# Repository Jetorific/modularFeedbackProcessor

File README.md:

# modularFeedbackProcessor
A Eurorack module that delays audio and allows the user to have their own custom effects in the feedback path. All analog design.

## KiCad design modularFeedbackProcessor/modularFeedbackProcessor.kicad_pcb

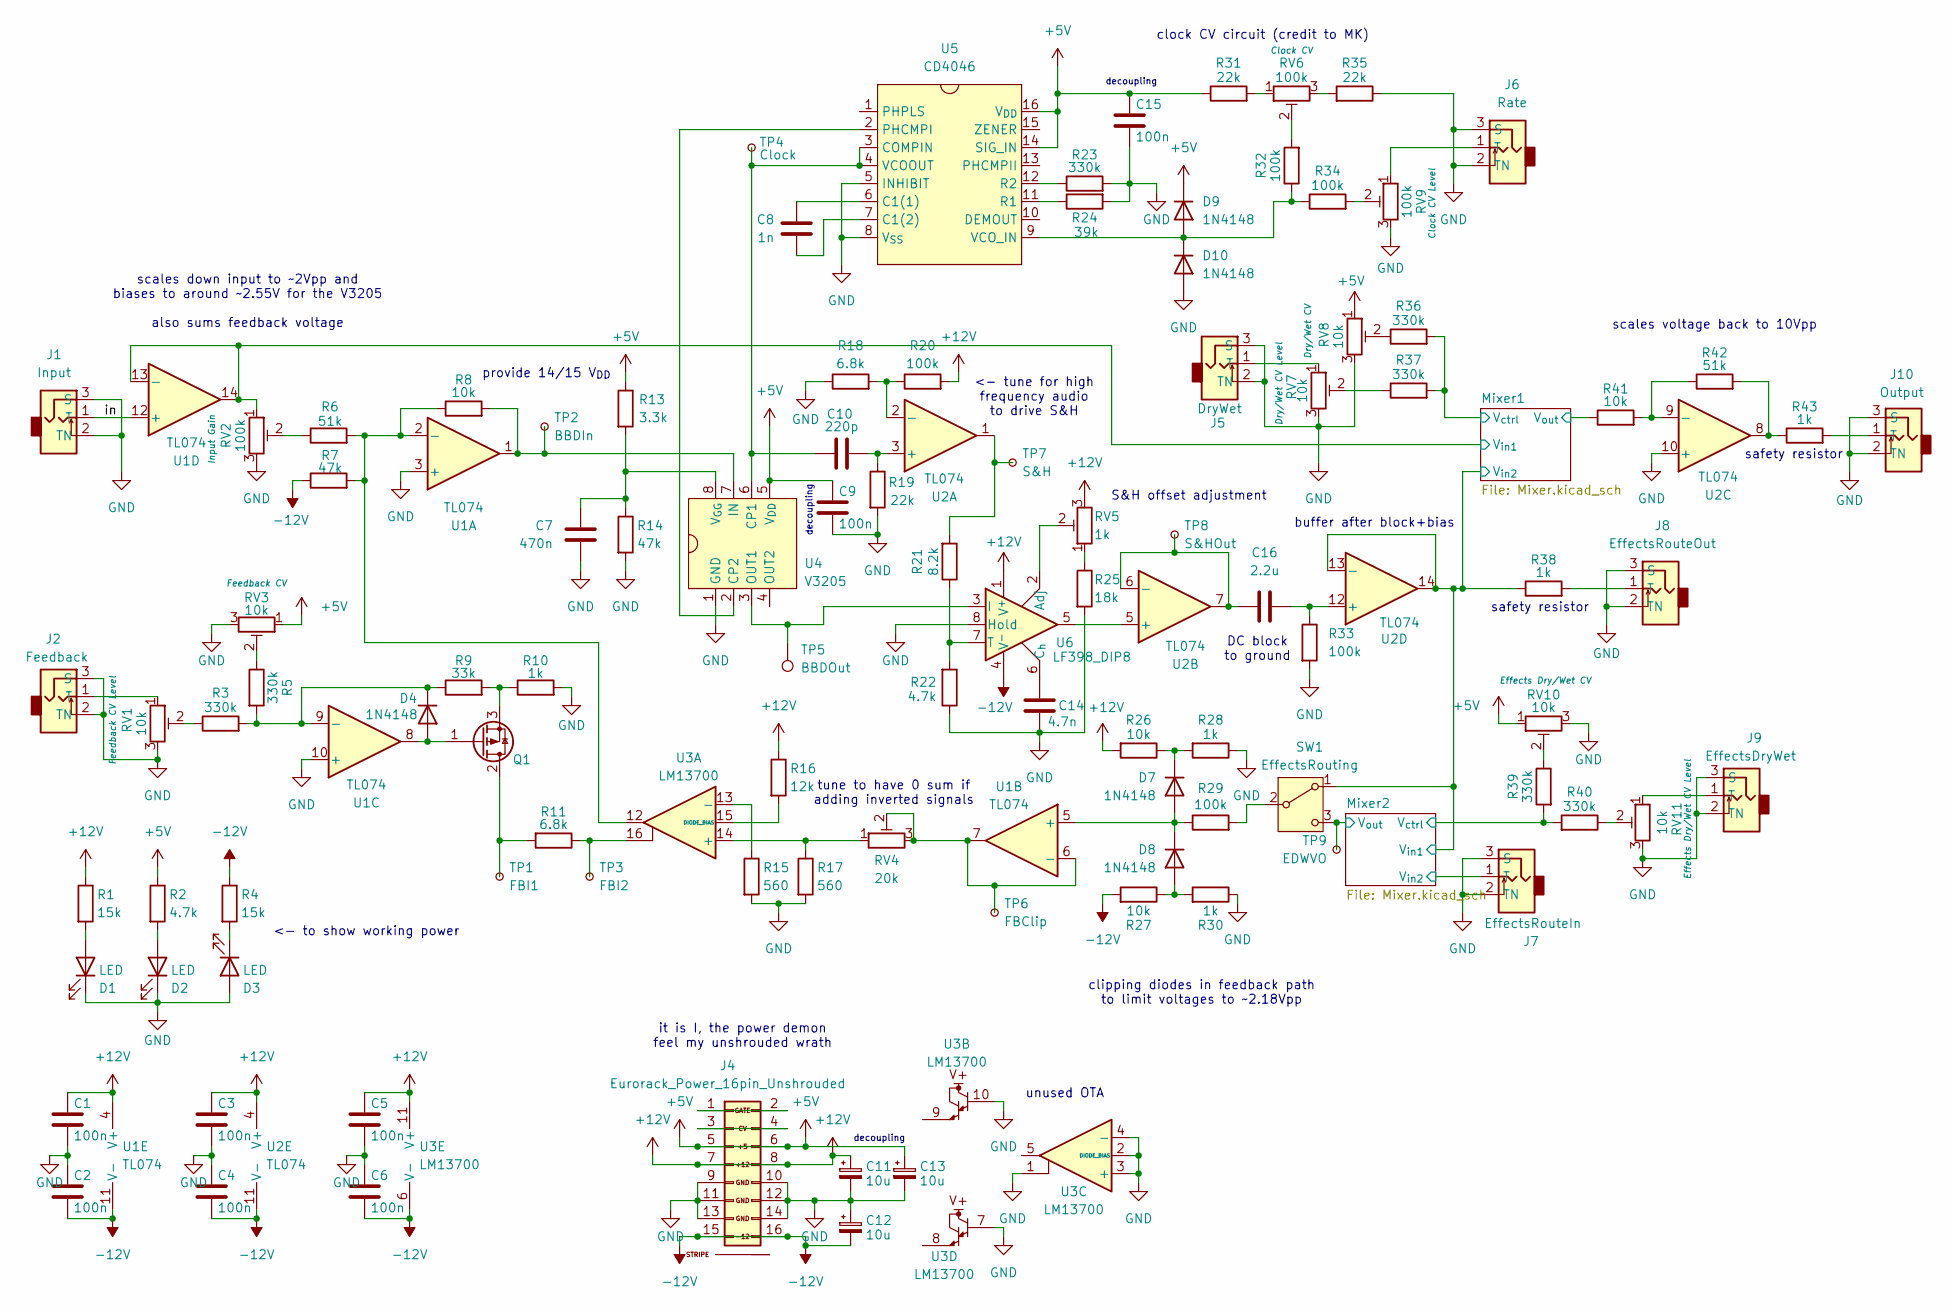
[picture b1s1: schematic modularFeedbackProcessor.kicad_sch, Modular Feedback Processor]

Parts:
C1, C2, C3, C4, C5, C6, C9, C15: 100n; C_0805_2012Metric_Pad1.18x1.45mm_HandSolder
C7: 470n; C_0805_2012Metric_Pad1.18x1.45mm_HandSolder
C8: 1n; C_0805_2012Metric_Pad1.18x1.45mm_HandSolder
C10: 220p; C_0805_2012Metric_Pad1.18x1.45mm_HandSolder
C11, C12, C13: 10u; CP_Radial_D5.0mm_P2.00mm
C14: 4.7n; C_0805_2012Metric_Pad1.18x1.45mm_HandSolder
C16: 2.2u; C_0805_2012Metric_Pad1.18x1.45mm_HandSolder
D1, D2, D3: LED; LED_D5.0mm
D4, D7, D8, D9, D10: 1N4148; D_DO-35_SOD27_P7.62mm_Horizontal
J1: Input; PJ301M-12
J2: Feedback; PJ301M-12
J4: Eurorack_Power_16pin_Unshrouded; Pins_2x08_2.54mm_TH_EuroPower; Part Number 1-1602FBV0T
J5: DryWet; PJ301M-12
J6: Rate; PJ301M-12
J7: EffectsRouteIn; PJ301M-12
J8: EffectsRouteOut; PJ301M-12
J9: EffectsDryWet; PJ301M-12
J10: Output; PJ301M-12
Q1: Q_PMOS_GDS; TO-220-3_Vertical
R1, R4: 15k; R_0805_2012Metric_Pad1.20x1.40mm_HandSolder
R2, R22: 4.7k; R_0805_2012Metric_Pad1.20x1.40mm_HandSolder
R3, R5, R23, R36, R37, R39, R40: 330k; R_0805_2012Metric_Pad1.20x1.40mm_HandSolder
R6, R42: 51k; R_0805_2012Metric_Pad1.20x1.40mm_HandSolder
R7, R14: 47k; R_0805_2012Metric_Pad1.20x1.40mm_HandSolder
R8, R26, R27, R41: 10k; R_0805_2012Metric_Pad1.20x1.40mm_HandSolder
R9: 33k; R_0805_2012Metric_Pad1.20x1.40mm_HandSolder
R10, R28, R30, R38, R43: 1k; R_0805_2012Metric_Pad1.20x1.40mm_HandSolder
R11, R18: 6.8k; R_0805_2012Metric_Pad1.20x1.40mm_HandSolder
R13: 3.3k; R_0805_2012Metric_Pad1.20x1.40mm_HandSolder
R15, R17: 560; R_0805_2012Metric_Pad1.20x1.40mm_HandSolder
R16: 12k; R_0805_2012Metric_Pad1.20x1.40mm_HandSolder
R19, R31, R35: 22k; R_0805_2012Metric_Pad1.20x1.40mm_HandSolder
R20, R29, R32, R33, R34: 100k; R_0805_2012Metric_Pad1.20x1.40mm_HandSolder
R21: 8.2k; R_0805_2012Metric_Pad1.20x1.40mm_HandSolder
R24: 39k; R_0805_2012Metric_Pad1.20x1.40mm_HandSolder
R25: 18k; R_0805_2012Metric_Pad1.20x1.40mm_HandSolder
RV1, RV3, RV7, RV8, RV10, RV11: 10k; Alpha9mmPot
RV2, RV6, RV9: 100k; Alpha9mmPot
RV4: 20k; Potentiometer_Vishay_T73XW_Horizontal
RV5: 1k; Potentiometer_Vishay_T73XW_Horizontal
SW1: EffectsRouting; Switch_Toggle_SPDT_SubMini
TP1: FBI1; TestPoint_Pad_06
TP2: BBDIn; TestPoint_Pad_06
TP3: FBI2; TestPoint_Pad_06
TP4: Clock; TestPoint_Pad_06
TP5: BBDOut; TestPoint_Pad_06
TP6: FBClip; TestPoint_Pad_06
TP7: S&H; TestPoint_Pad_06
TP8: S&HOut; TestPoint_Pad_06
TP9: EDWVO; TestPoint_Pad_06
U1, U2: TL074; DIP-14_W7.62mm_LongPads
U3: LM13700; DIP-16_W7.62mm_LongPads
U4: V3205; DIP-14_W7.62mm_LongPads_8pin
U5: CD4046; DIP-16_W7.62mm_LongPads
U6: LF398_DIP8; DIP-8_W7.62mm

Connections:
+5V: C9.1, C13.1, C15.1, D9.1 (K), J4.5 (+12V), J4.6, R2.1, R13.1, R31.1, RV3.1, RV8.1, RV10.1, U4.5 (V_{DD}), U5.14 (SIG_IN), U5.16 (V_{DD})
+12V: C1.1, C3.1, C5.1, C11.1, J4.7 (12V), J4.8 (+12V), R1.1, R16.1, R20.2, R26.2, RV5.3, U1.4 (V+), U2.4 (V+), U3.11 (V+), U6.1 (V^{+}); also elsewhere on the board
-12V: C2.2, C4.2, C6.2, C12.2, J4.15 (-12V), J4.16, R4.1, R7.1, R27.2, U1.11 (V-), U2.11 (V-), U3.6 (V-), U6.4 (V^{-}); also elsewhere on the board
/Mixer1/V_{ctrl}: R36.2, R37.2; also elsewhere on the board
/Mixer1/V_{in1}: RV2.1, U1.13 (-), U1.14; also elsewhere on the board
/Mixer1/V_{in2}: R38.1, SW1.1 (A), U2.13 (-), U2.14; also elsewhere on the board
/Mixer1/V_{out}: R41.1; also elsewhere on the board
/Mixer2/V_{ctrl}: R39.2, R40.2; also elsewhere on the board
/Mixer2/V_{in2}: J7.1 (T); also elsewhere on the board
/Mixer2/V_{out}: SW1.3 (C), TP9.1 (1_1); also elsewhere on the board
/in: J1.1 (T), U1.12 (+)
GND: C1.2, C2.1, C3.2, C4.1, C5.2, C6.1, C7.2, C9.2, C11.2, C12.1, C13.2, C14.2, C15.2, D1.1 (K), D2.1 (K), D3.2 (A), D10.2 (A), J1.2 (TN), J1.3 (S), J2.2 (TN), J2.3 (S), J4.9 (GND), J4.10 (GND), J4.11 (GND), J4.12 (GND), J4.13 (-12), J4.14 (-12V), J5.2 (TN), J5.3 (S), J6.2 (TN), J6.3 (S), J7.2 (TN), J7.3 (S), J8.2 (TN), J8.3 (S), J9.2 (TN), J9.3 (S), J10.2 (TN), J10.3 (S), R10.2, R14.2, R15.2, R17.2, R18.1, R19.2, R22.1, R23.2, R24.2, R25.2, R28.1, R30.1, R33.2, R35.1, RV1.3, RV2.3, RV3.3, RV7.3, RV8.3, RV9.3, RV10.3, RV11.3, U1.3 (+), U1.10 (+), U2.10 (+), U3.1, U3.2 (DIODE_BIAS), U3.3 (+), U3.4 (-), U3.7, U3.10, U4.1 (GND), U5.5 (INHIBIT), U5.8 (V_{SS}), U6.8 (Hold); also elsewhere on the board
unnamed: D1.2 (A), R1.2
unnamed: D2.2 (A), R2.2
unnamed: D3.1 (K), R4.2
unnamed: D4.2 (A), Q1.1 (G), U1.8
unnamed: D4.1 (K), R3.2, R5.2, R9.1, U1.9 (-)
unnamed: D7.2 (A), D8.1 (K), R29.1, U1.5 (+)
unnamed: D7.1 (K), R26.1, R28.2
unnamed: D8.2 (A), R27.1, R30.2
unnamed: D9.2 (A), D10.1 (K), R32.1, R34.1, U5.9 (VCO_IN)
unnamed: J2.1 (T), RV1.1
unnamed: J4.1, J4.2
unnamed: J4.3, J4.4
unnamed: J5.1 (T), RV7.1
unnamed: J6.1 (T), RV9.1
unnamed: J8.1 (T), R38.2
unnamed: J9.1 (T), RV11.1
unnamed: J10.1 (T), R43.2
unnamed: Q1.2 (D), R11.2, TP1.1 (1_1)
unnamed: Q1.3 (S), R9.2, R10.1
unnamed: R3.1, RV1.2
unnamed: R5.1, RV3.2
unnamed: R6.1, RV2.2
unnamed: R11.1, TP3.1 (1_1), U3.16
unnamed: R21.2, TP7.1 (1_1), U2.1
unnamed: R25.1, RV5.1
unnamed: R31.2, RV6.1
unnamed: R32.2, RV6.2
unnamed: R34.2, RV9.2
unnamed: R35.2, RV6.3
unnamed: R36.1, RV8.2
unnamed: R37.1, RV7.2
unnamed: R39.1, RV10.2
unnamed: R40.1, RV11.2
unnamed: R42.2, R43.1, U2.8
unnamed: R29.2, SW1.2 (B)
unnamed: R6.2, R7.2, R8.1, U1.2 (-), U3.12
unnamed: RV4.2, RV4.3, TP6.1 (1_1), U1.6 (-), U1.7
unnamed: C10.2, R19.1, U2.3 (+)
unnamed: R18.2, R20.1, U2.2 (-)
unnamed: U2.5 (+), U6.5
unnamed: C16.2, TP8.1 (1_1), U2.6 (-), U2.7
unnamed: R41.2, R42.1, U2.9 (-)
unnamed: C16.1, R33.1, U2.12 (+)
unnamed: R17.1, RV4.1, U3.14 (+)
unnamed: R15.1, U3.13 (-)
unnamed: R16.2, U3.15 (DIODE_BIAS)
unnamed: C10.1, TP4.1 (1_1), U4.6 (CP1), U5.3 (COMPIN), U5.4 (VCOOUT)
unnamed: U4.2 (CP2), U5.2 (PHCMPI)
unnamed: R8.2, TP2.1 (1_1), U1.1, U4.7 (IN)
unnamed: TP5.1 (1_1), U4.3 (OUT1), U6.3 (I)
unnamed: C7.1, R13.2, R14.1, U4.8 (V_{GG})
unnamed: C8.1, U5.6 (C1(1))
unnamed: C8.2, U5.7 (C1(2))
unnamed: R24.1, U5.11 (R1)
unnamed: R23.1, U5.12 (R2)
unnamed: RV5.2, U6.2 (Adj)
unnamed: C14.1, U6.6 (C_{h})
unnamed: R21.1, R22.2, U6.7 (T)

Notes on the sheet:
<- tune for high frequency audio to drive S&H
it is I, the power demon feel my unshrouded wrath
safety resistor
clock CV circuit (credit to MK)
unused OTA
clipping diodes in feedback path to limit voltages to ~2.18Vpp
decoupling
DC block to ground
scales voltage back to 10Vpp
<- to show working power
provide 14/15 V_{DD}
S&H offset adjustment
tune to have 0 sum if adding inverted signals
scales down input to ~2Vpp and biases to around ~2.55V for the V3205 also sums feedback voltage
buffer after block+bias

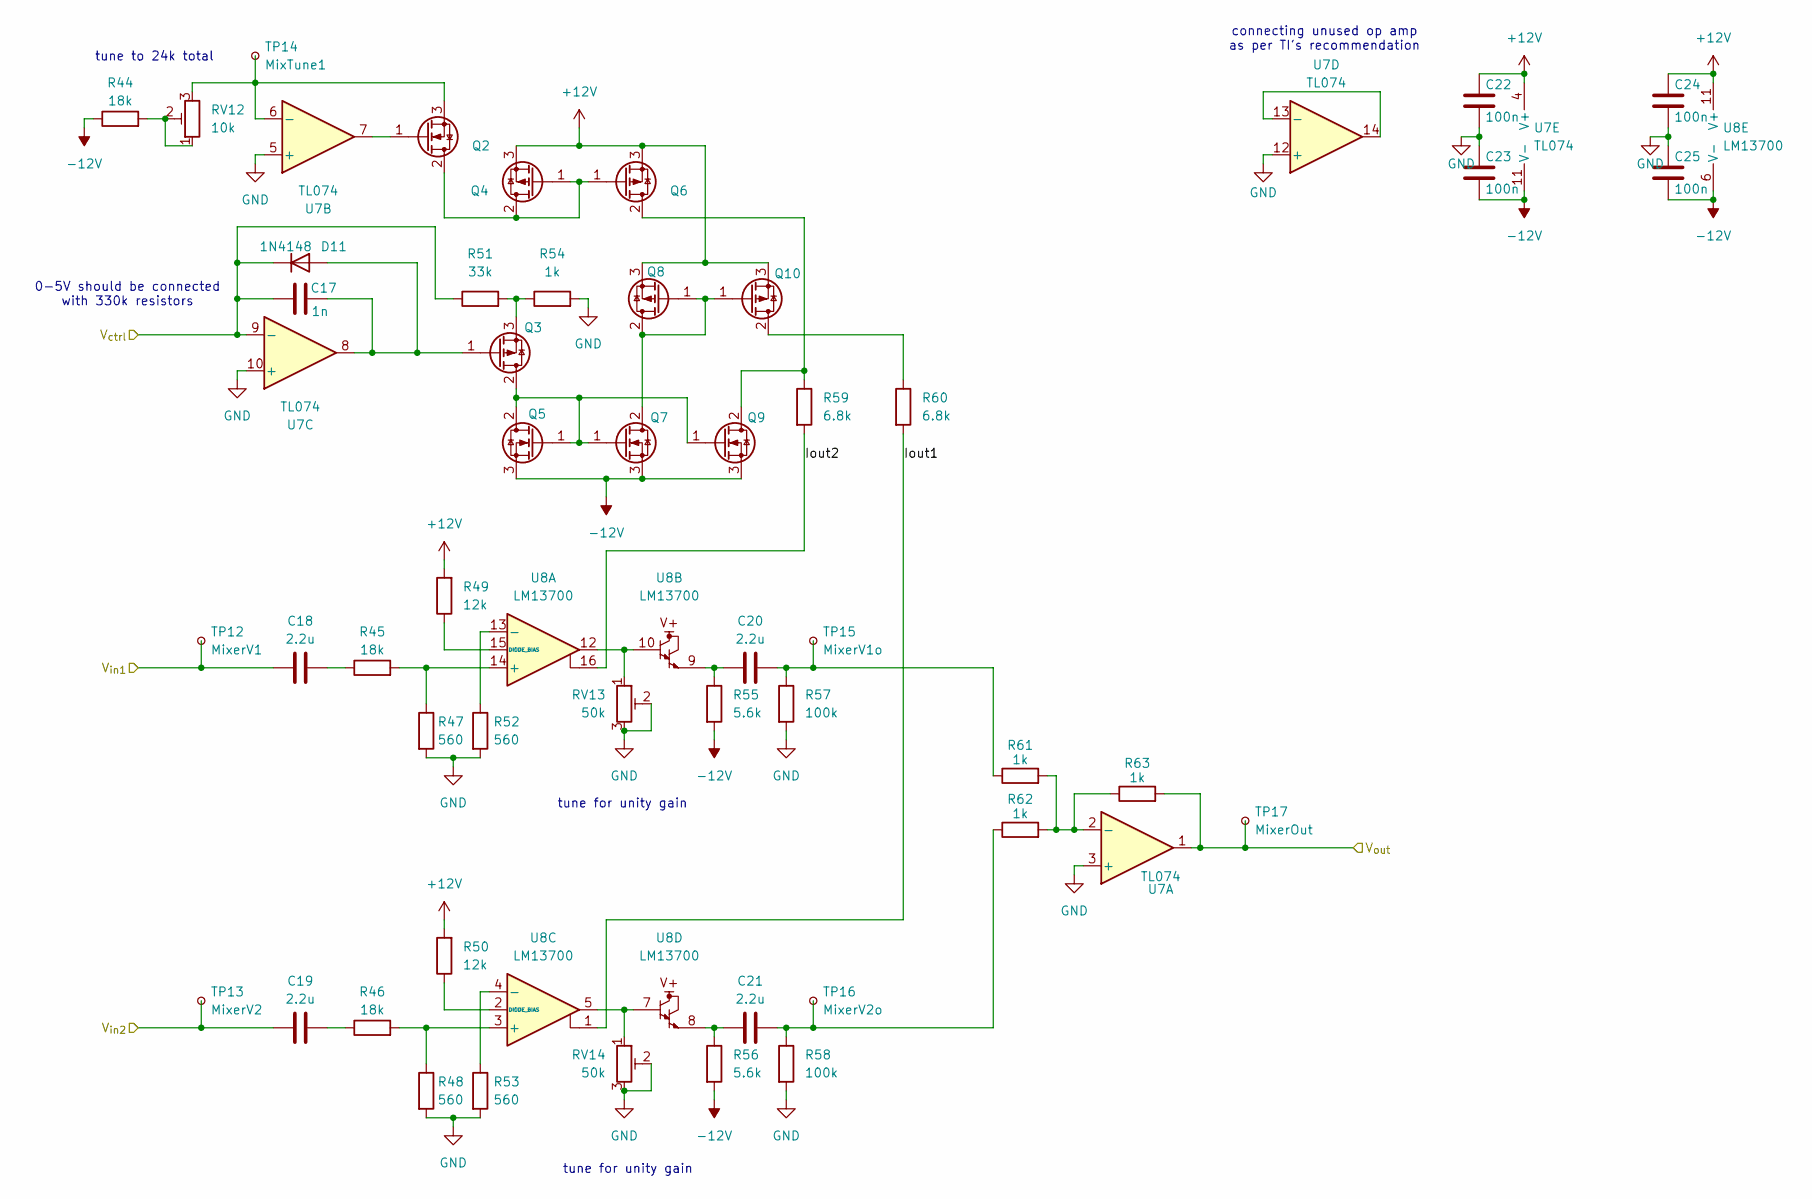
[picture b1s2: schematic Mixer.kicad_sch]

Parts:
C17: 1n; C_0805_2012Metric_Pad1.18x1.45mm_HandSolder
C18, C19, C20, C21: 2.2u; C_0805_2012Metric_Pad1.18x1.45mm_HandSolder
C22, C23, C24, C25: 100n; C_0805_2012Metric_Pad1.18x1.45mm_HandSolder
D11: 1N4148; D_DO-35_SOD27_P7.62mm_Horizontal
Q2, Q5, Q7, Q9: Q_NMOS_GDS; TO-220-3_Vertical
Q3, Q4, Q6, Q8, Q10: Q_PMOS_GDS; TO-220-3_Vertical
R44, R45, R46: 18k; R_0805_2012Metric_Pad1.20x1.40mm_HandSolder
R47, R48, R52, R53: 560; R_0805_2012Metric_Pad1.20x1.40mm_HandSolder
R49, R50: 12k; R_0805_2012Metric_Pad1.20x1.40mm_HandSolder
R51: 33k; R_0805_2012Metric_Pad1.20x1.40mm_HandSolder
R54, R61, R62, R63: 1k; R_0805_2012Metric_Pad1.20x1.40mm_HandSolder
R55, R56: 5.6k; R_0805_2012Metric_Pad1.20x1.40mm_HandSolder
R57, R58: 100k; R_0805_2012Metric_Pad1.20x1.40mm_HandSolder
R59, R60: 6.8k; R_0805_2012Metric_Pad1.20x1.40mm_HandSolder
RV12: 10k; Potentiometer_Vishay_T73XW_Horizontal
RV13, RV14: 50k; Potentiometer_Vishay_T73XW_Horizontal
TP12: MixerV1; TestPoint_Pad_06
TP13: MixerV2; TestPoint_Pad_06
TP14: MixTune1; TestPoint_Pad_06
TP15: MixerV1o; TestPoint_Pad_06
TP16: MixerV2o; TestPoint_Pad_06
TP17: MixerOut; TestPoint_Pad_06
U7: TL074; DIP-14_W7.62mm_LongPads
U8: LM13700; DIP-16_W7.62mm_LongPads

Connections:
+12V: C22.1, C24.1, Q4.3 (S), Q6.3 (S), Q8.3 (S), Q10.3 (S), R49.2, R50.2, U7.4 (V+), U8.11 (V+); also elsewhere on the board
-12V: C23.2, C25.2, Q5.3 (S), Q7.3 (S), Q9.3 (S), R44.1, R55.2, R56.2, U7.11 (V-), U8.6 (V-); also elsewhere on the board
/Mixer1/Iout1: R60.2, U8.1
/Mixer1/Iout2: R59.2, U8.16
/Mixer1/V_{ctrl}: C17.2, D11.1 (K), R51.1, U7.9 (-); also elsewhere on the board
/Mixer1/V_{in1}: C18.1, TP12.1 (1_1); also elsewhere on the board
/Mixer1/V_{in2}: C19.1, TP13.1 (1_1); also elsewhere on the board
/Mixer1/V_{out}: R63.2, TP17.1 (1_1), U7.1; also elsewhere on the board
GND: C22.2, C23.1, C24.2, C25.1, R47.2, R48.2, R52.2, R53.2, R54.2, R57.2, R58.2, RV13.2, RV13.3, RV14.2, RV14.3, U7.3 (+), U7.5 (+), U7.10 (+), U7.12 (+); also elsewhere on the board
unnamed: C18.2, R45.1
unnamed: C19.2, R46.1
unnamed: C20.1, R55.1, U8.9
unnamed: C20.2, R57.1, R61.1, TP15.1 (1_1)
unnamed: C21.1, R56.1, U8.8
unnamed: C21.2, R58.1, R62.1, TP16.1 (1_1)
unnamed: C17.1, D11.2 (A), Q3.1 (G), U7.8
unnamed: Q2.2 (D), Q4.1 (G), Q4.2 (D), Q6.1 (G)
unnamed: Q2.1 (G), U7.7
unnamed: Q2.3 (S), RV12.3, TP14.1 (1_1), U7.6 (-)
unnamed: Q3.2 (D), Q5.1 (G), Q5.2 (D), Q7.1 (G), Q9.1 (G)
unnamed: Q3.3 (S), R51.2, R54.1
unnamed: Q6.2 (D), Q9.2 (D), R59.1
unnamed: Q10.2 (D), R60.1
unnamed: Q7.2 (D), Q8.1 (G), Q8.2 (D), Q10.1 (G)
unnamed: R44.2, RV12.1, RV12.2
unnamed: RV13.1, U8.10, U8.12
unnamed: RV14.1, U8.5, U8.7
unnamed: R61.2, R62.2, R63.1, U7.2 (-)
unnamed: U7.13 (-), U7.14
unnamed: R45.2, R47.1, U8.14 (+)
unnamed: R52.1, U8.13 (-)
unnamed: R49.1, U8.15 (DIODE_BIAS)
unnamed: R46.2, R48.1, U8.3 (+)
unnamed: R53.1, U8.4 (-)
unnamed: R50.1, U8.2 (DIODE_BIAS)

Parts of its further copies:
C26: 1n; C_0805_2012Metric_Pad1.18x1.45mm_HandSolder
C27, C28, C29, C30: 2.2u; C_0805_2012Metric_Pad1.18x1.45mm_HandSolder
C31, C32, C33, C34: 100n; C_0805_2012Metric_Pad1.18x1.45mm_HandSolder
D12: 1N4148; D_DO-35_SOD27_P7.62mm_Horizontal
Q11, Q14, Q16, Q18: Q_NMOS_GDS; TO-220-3_Vertical
Q12, Q13, Q15, Q17, Q19: Q_PMOS_GDS; TO-220-3_Vertical
R64, R65, R66: 18k; R_0805_2012Metric_Pad1.20x1.40mm_HandSolder
R67, R68, R72, R73: 560; R_0805_2012Metric_Pad1.20x1.40mm_HandSolder
R69, R70: 12k; R_0805_2012Metric_Pad1.20x1.40mm_HandSolder
R71: 33k; R_0805_2012Metric_Pad1.20x1.40mm_HandSolder
R74, R81, R82, R83: 1k; R_0805_2012Metric_Pad1.20x1.40mm_HandSolder
R75, R76: 5.6k; R_0805_2012Metric_Pad1.20x1.40mm_HandSolder
R77, R78: 100k; R_0805_2012Metric_Pad1.20x1.40mm_HandSolder
R79, R80: 6.8k; R_0805_2012Metric_Pad1.20x1.40mm_HandSolder
RV15: 10k; Potentiometer_Vishay_T73XW_Horizontal
RV16, RV17: 50k; Potentiometer_Vishay_T73XW_Horizontal
TP18: MixerV1; TestPoint_Pad_06
TP19: MixerV2; TestPoint_Pad_06
TP20: MixTune1; TestPoint_Pad_06
TP21: MixerV1o; TestPoint_Pad_06
TP22: MixerV2o; TestPoint_Pad_06
TP23: MixerOut; TestPoint_Pad_06
U9: TL074; DIP-14_W7.62mm_LongPads
U10: LM13700; DIP-16_W7.62mm_LongPads

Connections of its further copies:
+12V: C31.1, C33.1, Q13.3 (S), Q15.3 (S), Q17.3 (S), Q19.3 (S), R69.2, R70.2, U9.4 (V+), U10.11 (V+); also elsewhere on the board
-12V: C32.2, C34.2, Q14.3 (S), Q16.3 (S), Q18.3 (S), R64.1, R75.2, R76.2, U9.11 (V-), U10.6 (V-); also elsewhere on the board
/Mixer1/V_{in2}: C27.1, TP18.1 (1_1); also elsewhere on the board
/Mixer2/Iout1: R80.2, U10.1
/Mixer2/Iout2: R79.2, U10.16
/Mixer2/V_{ctrl}: C26.2, D12.1 (K), R71.1, U9.9 (-); also elsewhere on the board
/Mixer2/V_{in2}: C28.1, TP19.1 (1_1); also elsewhere on the board
/Mixer2/V_{out}: R83.2, TP23.1 (1_1), U9.1; also elsewhere on the board
GND: C31.2, C32.1, C33.2, C34.1, R67.2, R68.2, R72.2, R73.2, R74.2, R77.2, R78.2, RV16.2, RV16.3, RV17.2, RV17.3, U9.3 (+), U9.5 (+), U9.10 (+), U9.12 (+); also elsewhere on the board
unnamed: C27.2, R65.1
unnamed: C28.2, R66.1
unnamed: C29.1, R75.1, U10.9
unnamed: C29.2, R77.1, R81.1, TP21.1 (1_1)
unnamed: C30.1, R76.1, U10.8
unnamed: C30.2, R78.1, R82.1, TP22.1 (1_1)
unnamed: C26.1, D12.2 (A), Q12.1 (G), U9.8
unnamed: Q11.2 (D), Q13.1 (G), Q13.2 (D), Q15.1 (G)
unnamed: Q11.1 (G), U9.7
unnamed: Q11.3 (S), RV15.3, TP20.1 (1_1), U9.6 (-)
unnamed: Q12.2 (D), Q14.1 (G), Q14.2 (D), Q16.1 (G), Q18.1 (G)
unnamed: Q12.3 (S), R71.2, R74.1
unnamed: Q15.2 (D), Q18.2 (D), R79.1
unnamed: Q16.2 (D), Q17.1 (G), Q17.2 (D), Q19.1 (G)
unnamed: Q19.2 (D), R80.1
unnamed: R64.2, RV15.1, RV15.2
unnamed: RV16.1, U10.10, U10.12
unnamed: RV17.1, U10.5, U10.7
unnamed: R81.2, R82.2, R83.1, U9.2 (-)
unnamed: U9.13 (-), U9.14
unnamed: R65.2, R67.1, U10.14 (+)
unnamed: R72.1, U10.13 (-)
unnamed: R69.1, U10.15 (DIODE_BIAS)
unnamed: R66.2, R68.1, U10.3 (+)
unnamed: R73.1, U10.4 (-)
unnamed: R70.1, U10.2 (DIODE_BIAS)

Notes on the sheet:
tune for unity gain
connecting unused op amp as per TI's recommendation
tune to 24k total
0-5V should be connected with 330k resistors

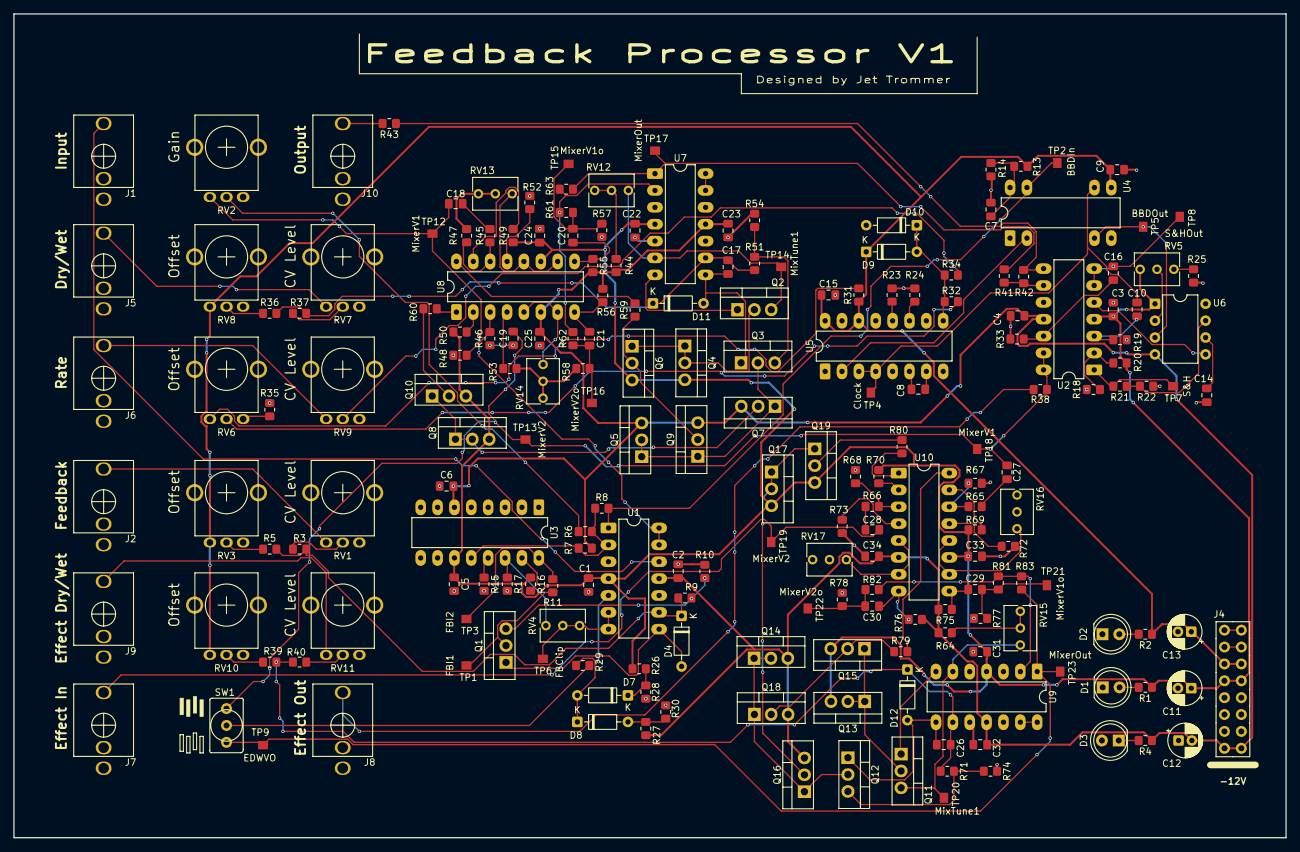
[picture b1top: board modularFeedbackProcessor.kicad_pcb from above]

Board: 2 copper layers, 191.5 x 124.0 mm, 203 parts (0 on the bottom side), 126 nets.

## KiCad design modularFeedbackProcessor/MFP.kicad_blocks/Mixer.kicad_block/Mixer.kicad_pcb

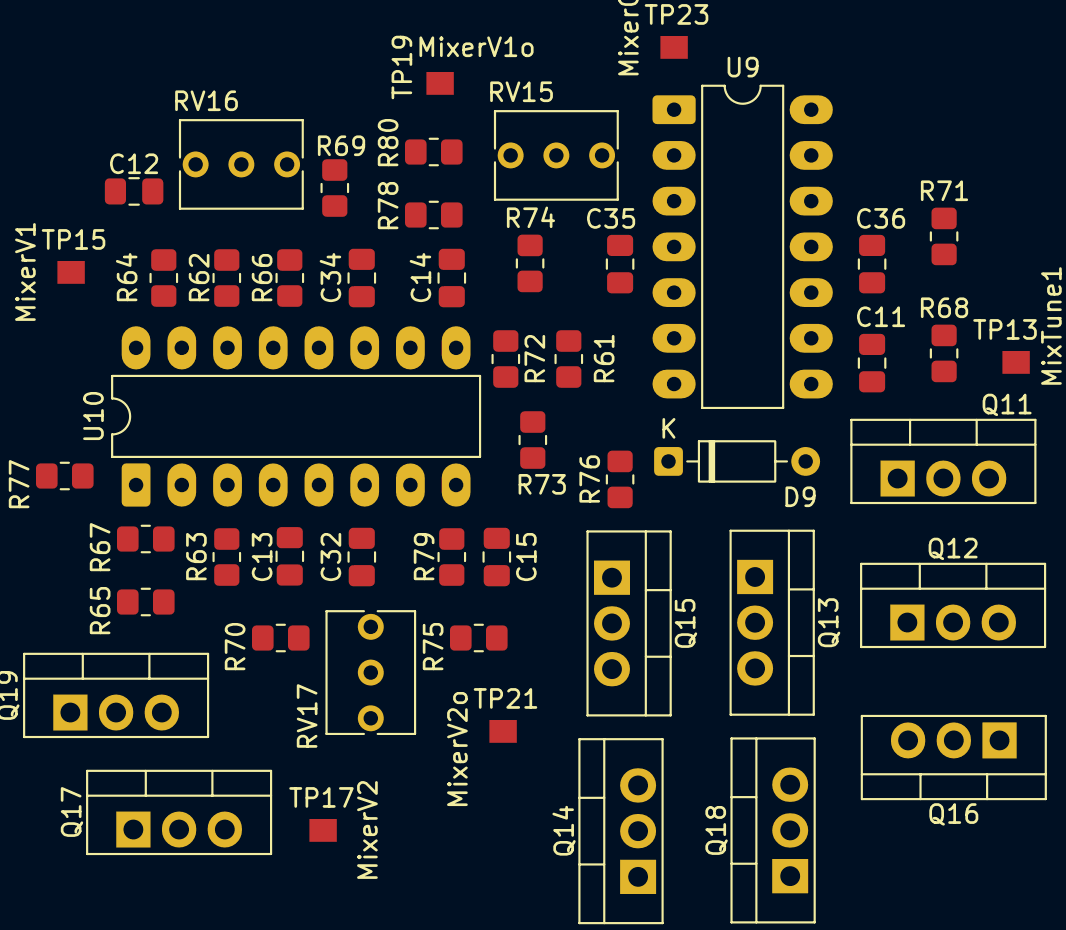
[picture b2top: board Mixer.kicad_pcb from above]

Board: 4 copper layers, 50 parts (0 on the bottom side), 35 nets, no tracks yet.

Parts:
C11: 1n; C_0805_2012Metric_Pad1.18x1.45mm_HandSolder
C12, C13, C14, C15: 2.2u; C_0805_2012Metric_Pad1.18x1.45mm_HandSolder
C32, C34, C35, C36: 100n; C_0805_2012Metric_Pad1.18x1.45mm_HandSolder
D9: 1N4148; D_DO-35_SOD27_P7.62mm_Horizontal
Q11, Q14, Q16, Q18: Q_NMOS_GDS; TO-220-3_Vertical
Q12, Q13, Q15, Q17, Q19: Q_PMOS_GDS; TO-220-3_Vertical
R61, R62, R63: 18k; R_0805_2012Metric_Pad1.20x1.40mm_HandSolder
R64, R65, R69, R70: 560; R_0805_2012Metric_Pad1.20x1.40mm_HandSolder
R66, R67: 12k; R_0805_2012Metric_Pad1.20x1.40mm_HandSolder
R68: 33k; R_0805_2012Metric_Pad1.20x1.40mm_HandSolder
R71, R78, R79, R80: 1k; R_0805_2012Metric_Pad1.20x1.40mm_HandSolder
R72, R73: 5.6k; R_0805_2012Metric_Pad1.20x1.40mm_HandSolder
R74, R75: 100k; R_0805_2012Metric_Pad1.20x1.40mm_HandSolder
R76, R77: 6.8k; R_0805_2012Metric_Pad1.20x1.40mm_HandSolder
RV15: 10k; Potentiometer_Vishay_T73XW_Horizontal
RV16, RV17: 50k; Potentiometer_Vishay_T73XW_Horizontal
TP13: MixTune1; TestPoint_Pad_06
TP15: MixerV1; TestPoint_Pad_06
TP17: MixerV2; TestPoint_Pad_06
TP19: MixerV1o; TestPoint_Pad_06
TP21: MixerV2o; TestPoint_Pad_06
TP23: MixerOut; TestPoint_Pad_06
U9: TL074; DIP-14_W7.62mm_LongPads
U10: LM13700; DIP-16_W7.62mm_LongPads

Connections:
+12V: C34.1, C35.1, Q13.3 (S), Q15.3 (S), Q17.3 (S), Q19.3 (S), R66.2, R67.2, U9.4 (V+), U10.11 (V+)
-12V: C32.2, C36.2, Q14.3 (S), Q16.3 (S), Q18.3 (S), R61.1, R72.2, R73.2, U9.11 (V-), U10.6 (V-)
/DryWet Mixer/V_{in2}: C12.1, TP15.1 (1_1)
/Effects Mixer/Iout1: R77.2, U10.1
/Effects Mixer/Iout2: R76.2, U10.16
/Effects Mixer/V_{ctrl}: C11.2, D9.1 (K), R68.1, U9.9 (-)
/Effects Mixer/V_{in2}: C13.1, TP17.1 (1_1)
/Effects Mixer/V_{out}: R80.2, TP23.1 (1_1), U9.1
GND: C32.1, C34.2, C35.2, C36.1, R64.2, R65.2, R69.2, R70.2, R71.2, R74.2, R75.2, RV16.2, RV16.3, RV17.2, RV17.3, U9.3 (+), U9.5 (+), U9.10 (+), U9.12 (+)
unnamed: C12.2, R62.1
unnamed: C13.2, R63.1
unnamed: C14.1, R72.1, U10.9
unnamed: C14.2, R74.1, R78.1, TP19.1 (1_1)
unnamed: C15.1, R73.1, U10.8
unnamed: C15.2, R75.1, R79.1, TP21.1 (1_1)
unnamed: C11.1, D9.2 (A), Q12.1 (G), U9.8
unnamed: Q11.2 (D), Q13.1 (G), Q13.2 (D), Q15.1 (G)
unnamed: Q11.1 (G), U9.7
unnamed: Q11.3 (S), RV15.3, TP13.1 (1_1), U9.6 (-)
unnamed: Q12.2 (D), Q14.1 (G), Q14.2 (D), Q16.1 (G), Q18.1 (G)
unnamed: Q12.3 (S), R68.2, R71.1
unnamed: Q15.2 (D), Q18.2 (D), R76.1
unnamed: Q16.2 (D), Q17.1 (G), Q17.2 (D), Q19.1 (G)
unnamed: Q19.2 (D), R77.1
unnamed: R61.2, RV15.1, RV15.2
unnamed: RV16.1, U10.10, U10.12
unnamed: RV17.1, U10.5, U10.7
unnamed: R78.2, R79.2, R80.1, U9.2 (-)
unnamed: U9.13 (-), U9.14
unnamed: R62.2, R64.1, U10.14 (+)
unnamed: R69.1, U10.13 (-)
unnamed: R66.1, U10.15 (DIODE_BIAS)
unnamed: R63.2, R65.1, U10.3 (+)
unnamed: R70.1, U10.4 (-)
unnamed: R67.1, U10.2 (DIODE_BIAS)

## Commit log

2026-04-04 Added linked mixer submodule.
2026-04-04 Scaling down input from 10Vpp to 1Vpp
2026-04-07 Tuesday commit
2026-04-07 added basic CV control for single linked mixer
2026-04-07 Minor changes + clock CV rework based on Moritz Klein's work
2026-04-07 some CV work
2026-04-07 last lab changes. slightly more text
2026-04-15 committing from macbook, KiCad 10.0
2026-04-21 feedback path completed without effects routing
2026-04-21 basically finished the thing? added full feedback path. all jacks are routed (except for double)
2026-04-21 more fixes, touch ups. implemented rescaling of the output.
2026-04-21 added switch to turn on/off effect routing
2026-04-22 pushing changes
2026-04-22 fixed 6.8k resistor location in feedback VCA
2026-04-22 last commit before attempting to change the S&H to the LF398
2026-04-22 added all footprints, beginning to work on ERC errors
2026-04-23 lots of friggin progress. finished footprint work, and have just finished grouping. Now I will start to connect each group internally.
2026-04-23 save before i mess something up
2026-04-23 Update: did not destroy everything
2026-04-23 layout mostly down. Going to begin routing
2026-04-23 routed power, good start
2026-04-23 mostly done with the BBD module routing
2026-04-23 significant progress
2026-04-23 first version to pass DRC
2026-04-23 save before 220 class
2026-04-23 forgot to save schematic
2026-04-23 finished final tweaks before JLC
2026-04-23 oops final one
2026-04-24 Fixed error with Q1. Drain/source were swapped. Unfortunately the PCB will not receive such fixing before it arrives.
2026-04-27 fixed Q1 on PCB.
2026-04-29 fixed a few things
2026-04-30 saving before I start fixing things
2026-04-30 Added DC blocking capacitor in S&H. Changed S&H sampling cap to 10n
2026-05-01 Added resistors for DC blocking cap. Added decoupling caps for LF398.
2026-05-01 swapped pins 7 and 8 of LF398
